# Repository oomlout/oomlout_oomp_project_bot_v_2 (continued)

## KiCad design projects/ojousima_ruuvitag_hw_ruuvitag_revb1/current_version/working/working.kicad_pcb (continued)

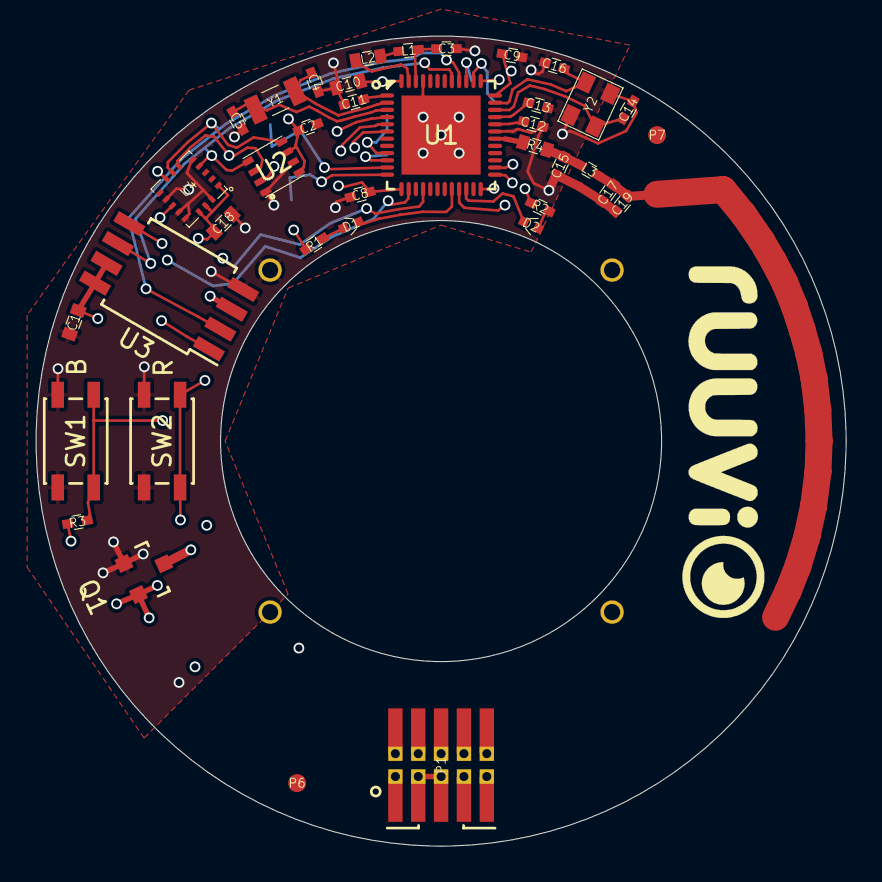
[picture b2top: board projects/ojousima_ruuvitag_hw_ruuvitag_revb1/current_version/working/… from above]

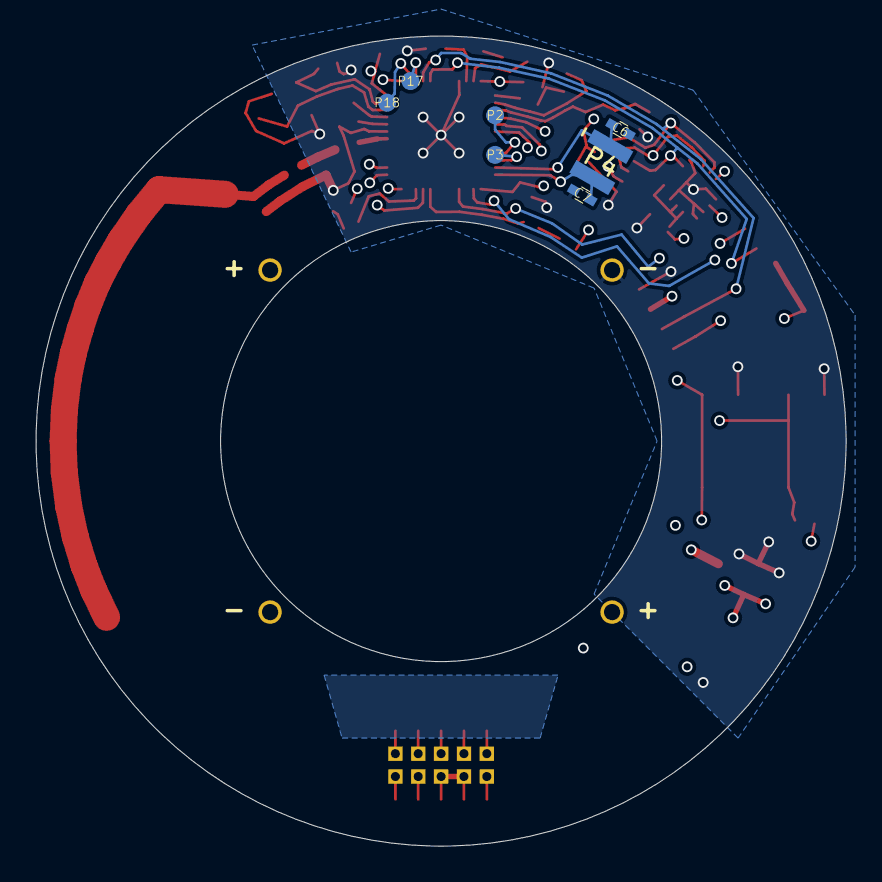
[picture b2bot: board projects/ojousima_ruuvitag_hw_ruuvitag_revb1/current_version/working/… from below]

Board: 4 copper layers, 45.0 x 45.0 mm, 49 parts (7 on the bottom side), 38 nets.

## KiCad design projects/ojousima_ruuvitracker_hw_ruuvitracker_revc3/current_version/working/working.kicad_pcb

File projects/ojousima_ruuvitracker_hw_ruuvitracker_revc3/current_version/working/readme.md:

# ruuvitracker_hw
 
## summary 
* id: ojousima_ruuvitracker_hw_ruuvitracker_revc3
* user: ojousima
* name: ruuvitracker_hw
* board: ruuvitracker_revc3
* repo: https://github.com/ojousima/ruuvitracker_hw
* src_file_repo_kicad_pcb: ruuvitracker_revc3/ruuvitracker_revc3.kicad_pcb
* src_file_repo_kicad_pcb_link: https://github.com/ojousima/ruuvitracker_hw/tree/master/ruuvitracker_revc3/ruuvitracker_revc3.kicad_pcb

* src_file_repo_sch: ruuvitracker_revc3/ruuvitracker_revc3.sch
* src_file_repo_sch_link: https://github.com/ojousima/ruuvitracker_hw/tree/master/ruuvitracker_revc3/ruuvitracker_revc3.sch
* full details link: https://github.com/oomlout/oomlout_oomp_project_bot_v_2/tree/main/projects/ojousima_ruuvitracker_hw_ruuvitracker_revc3/current_version/working

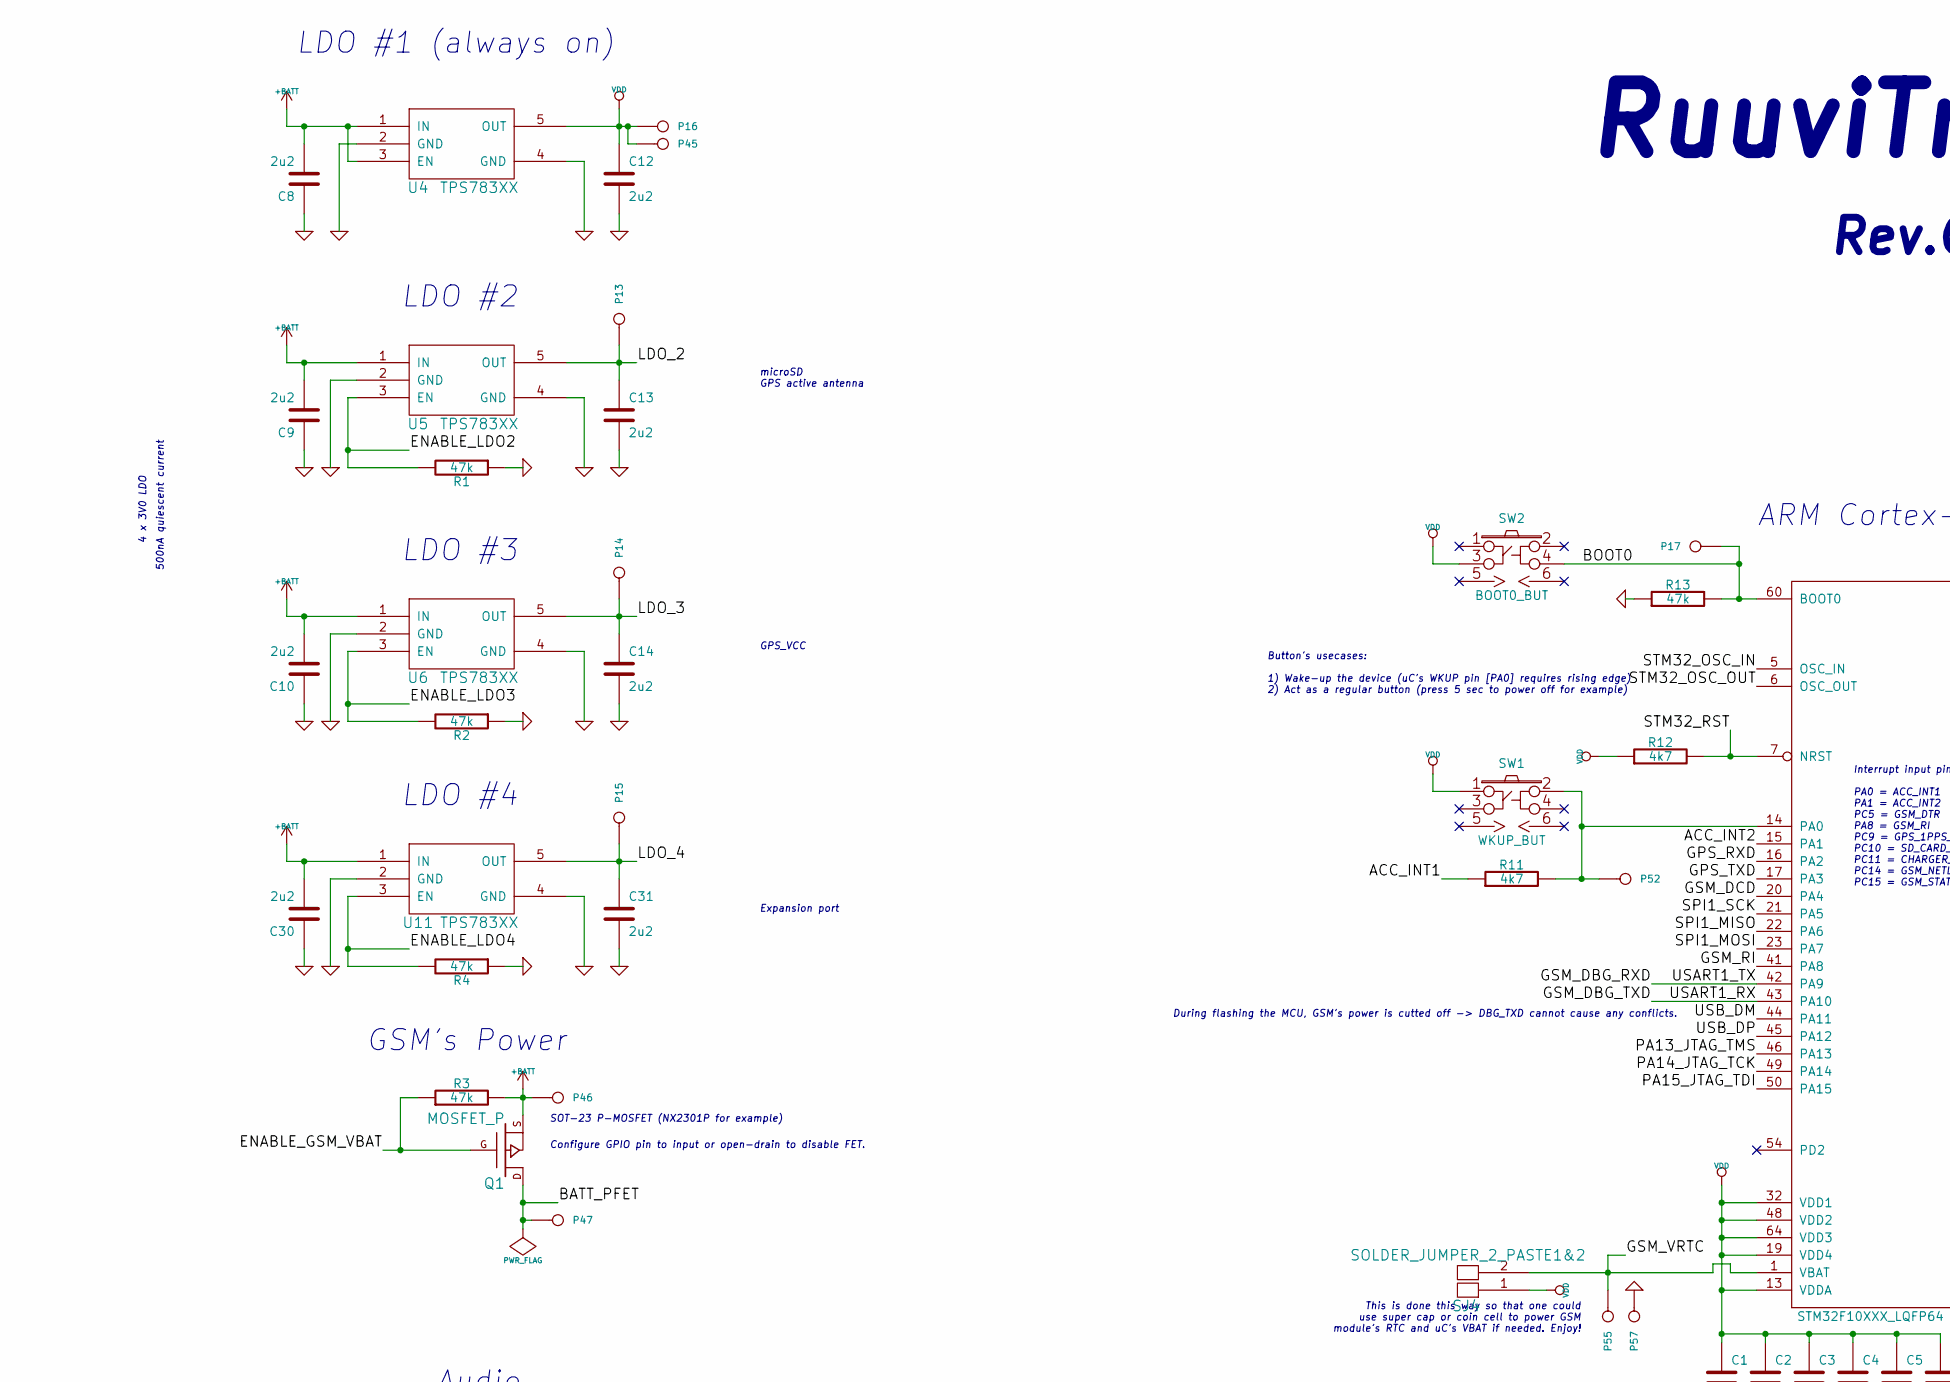
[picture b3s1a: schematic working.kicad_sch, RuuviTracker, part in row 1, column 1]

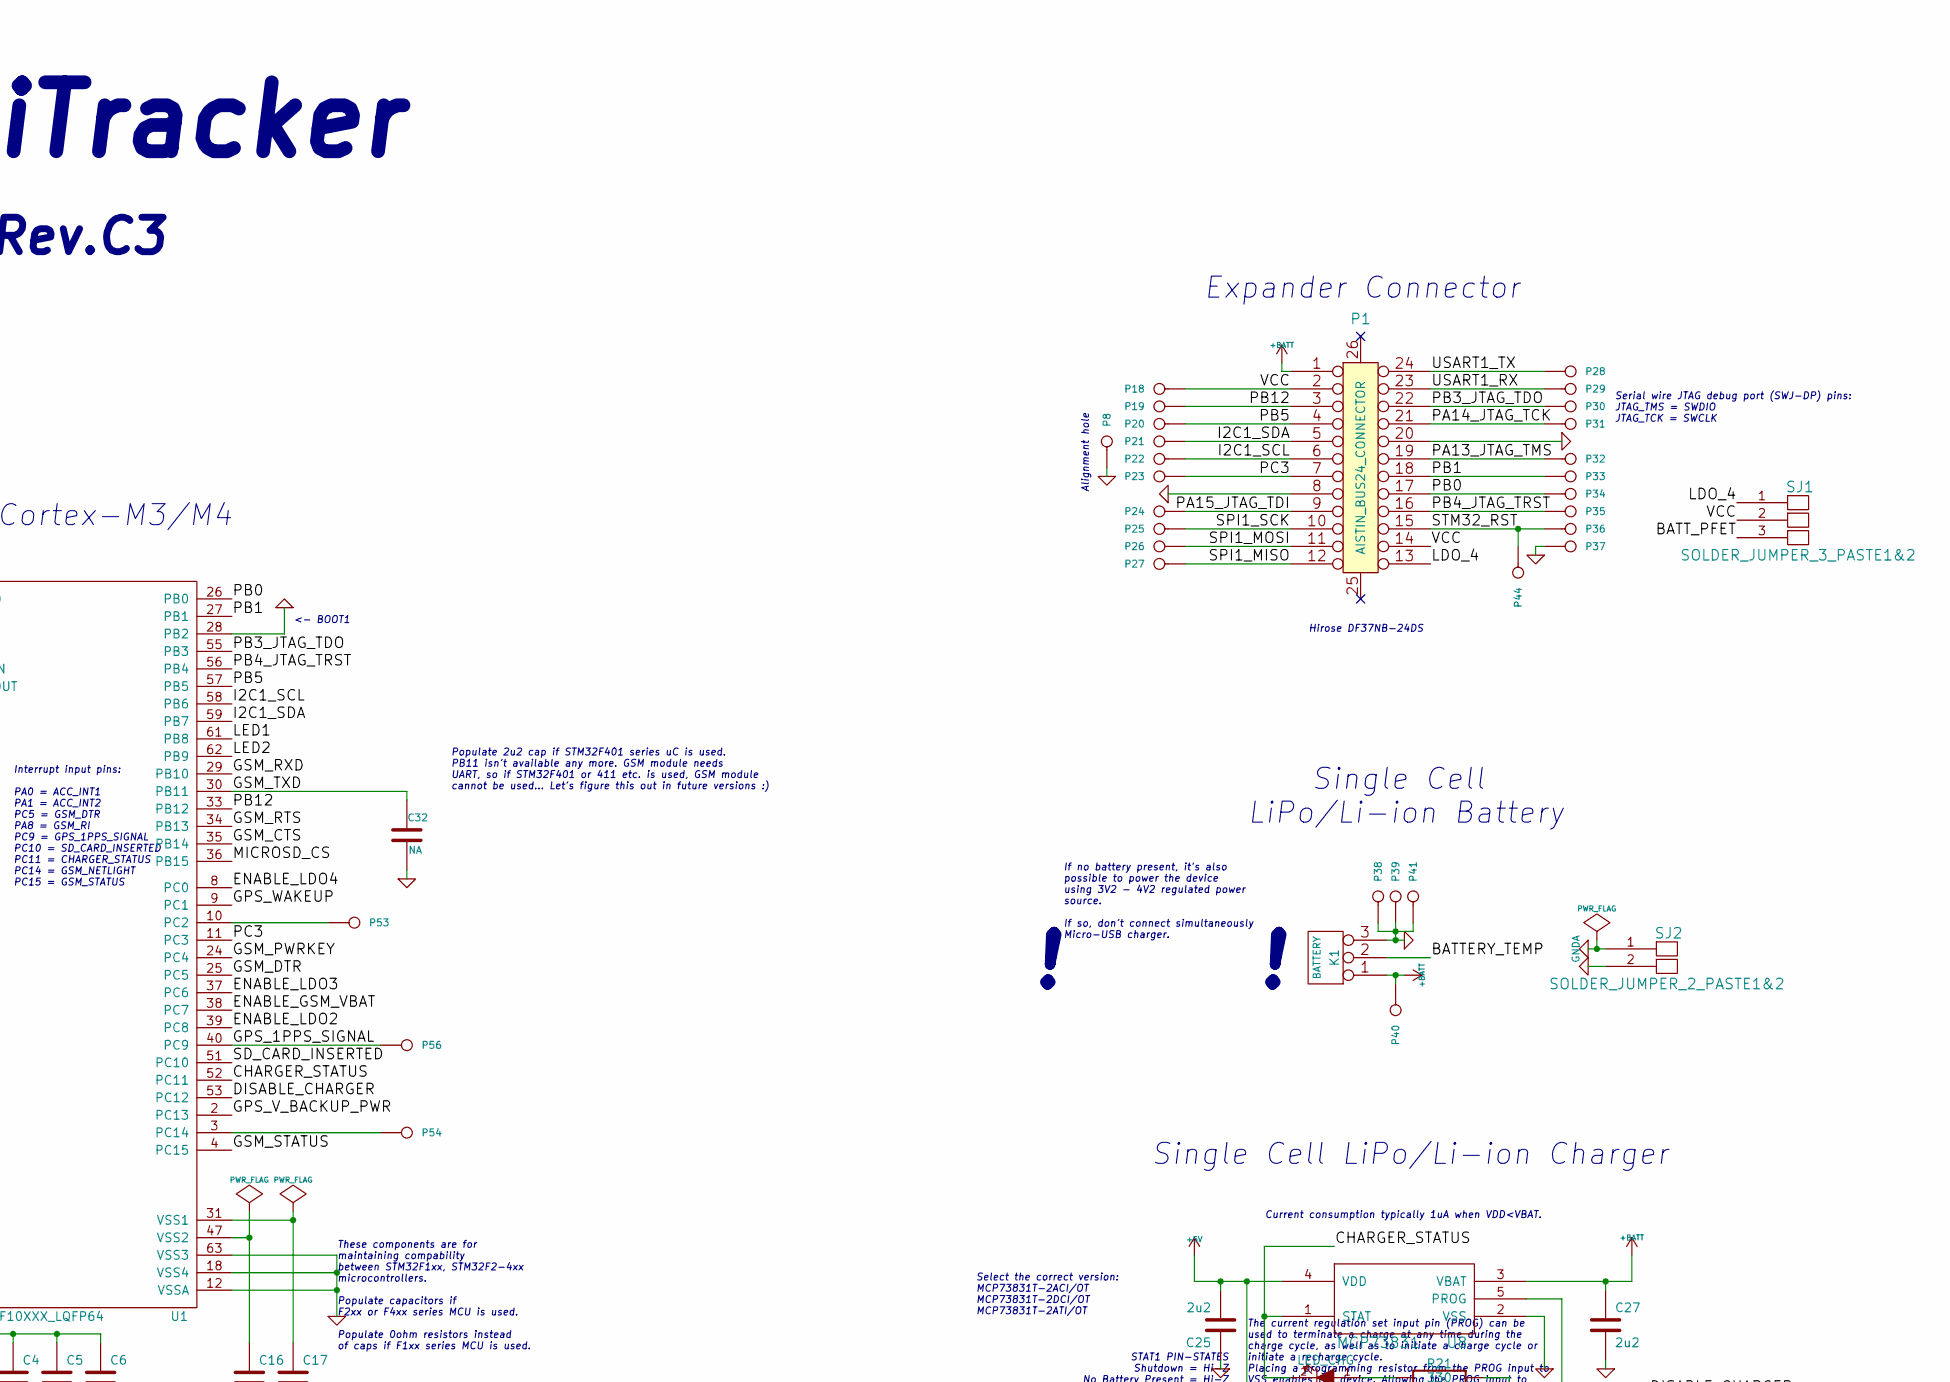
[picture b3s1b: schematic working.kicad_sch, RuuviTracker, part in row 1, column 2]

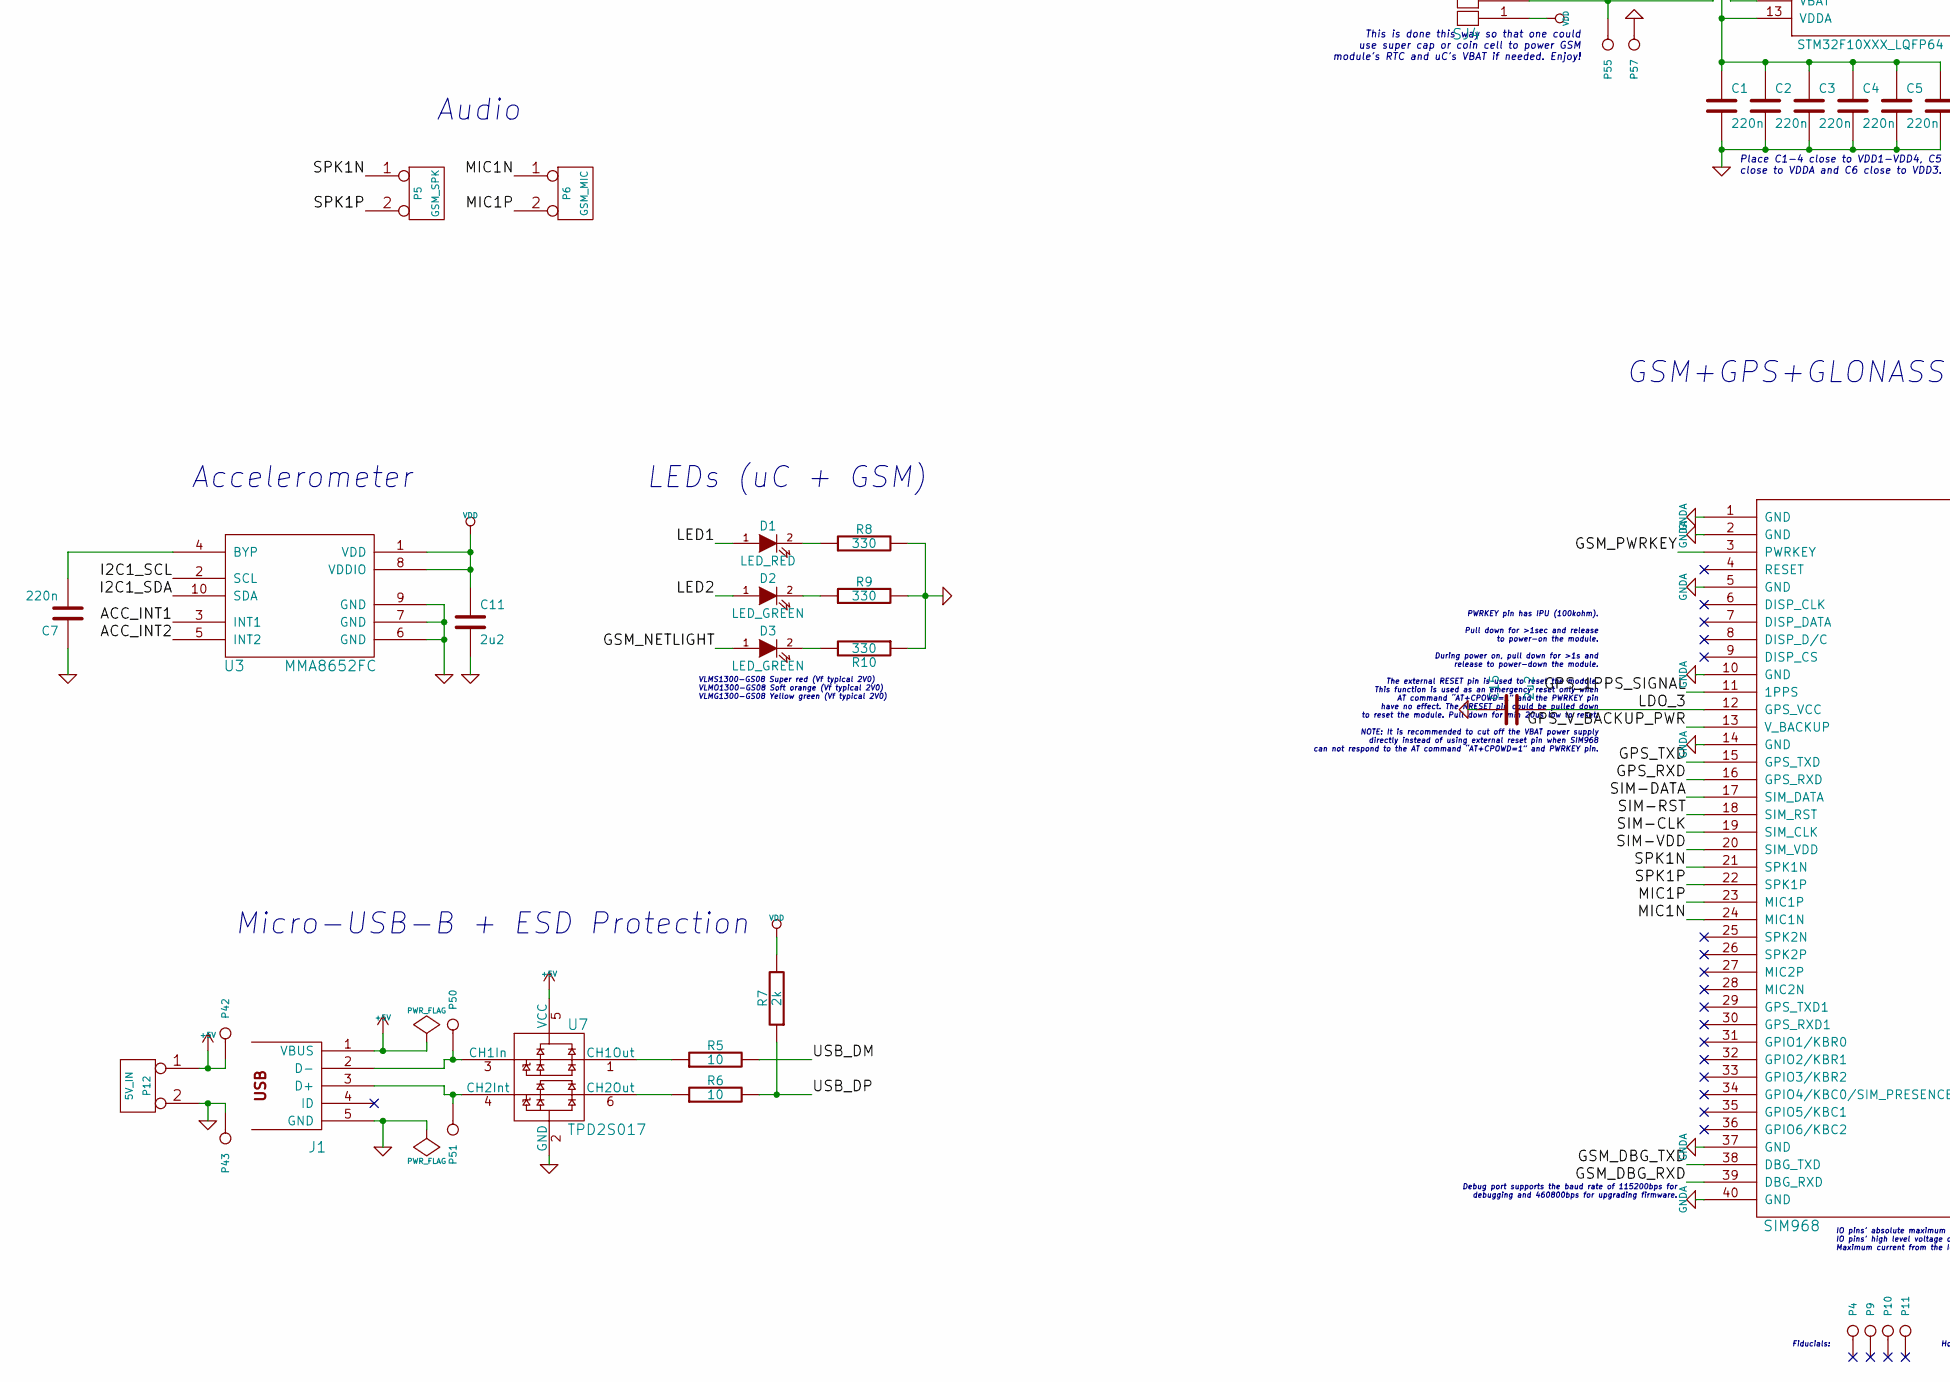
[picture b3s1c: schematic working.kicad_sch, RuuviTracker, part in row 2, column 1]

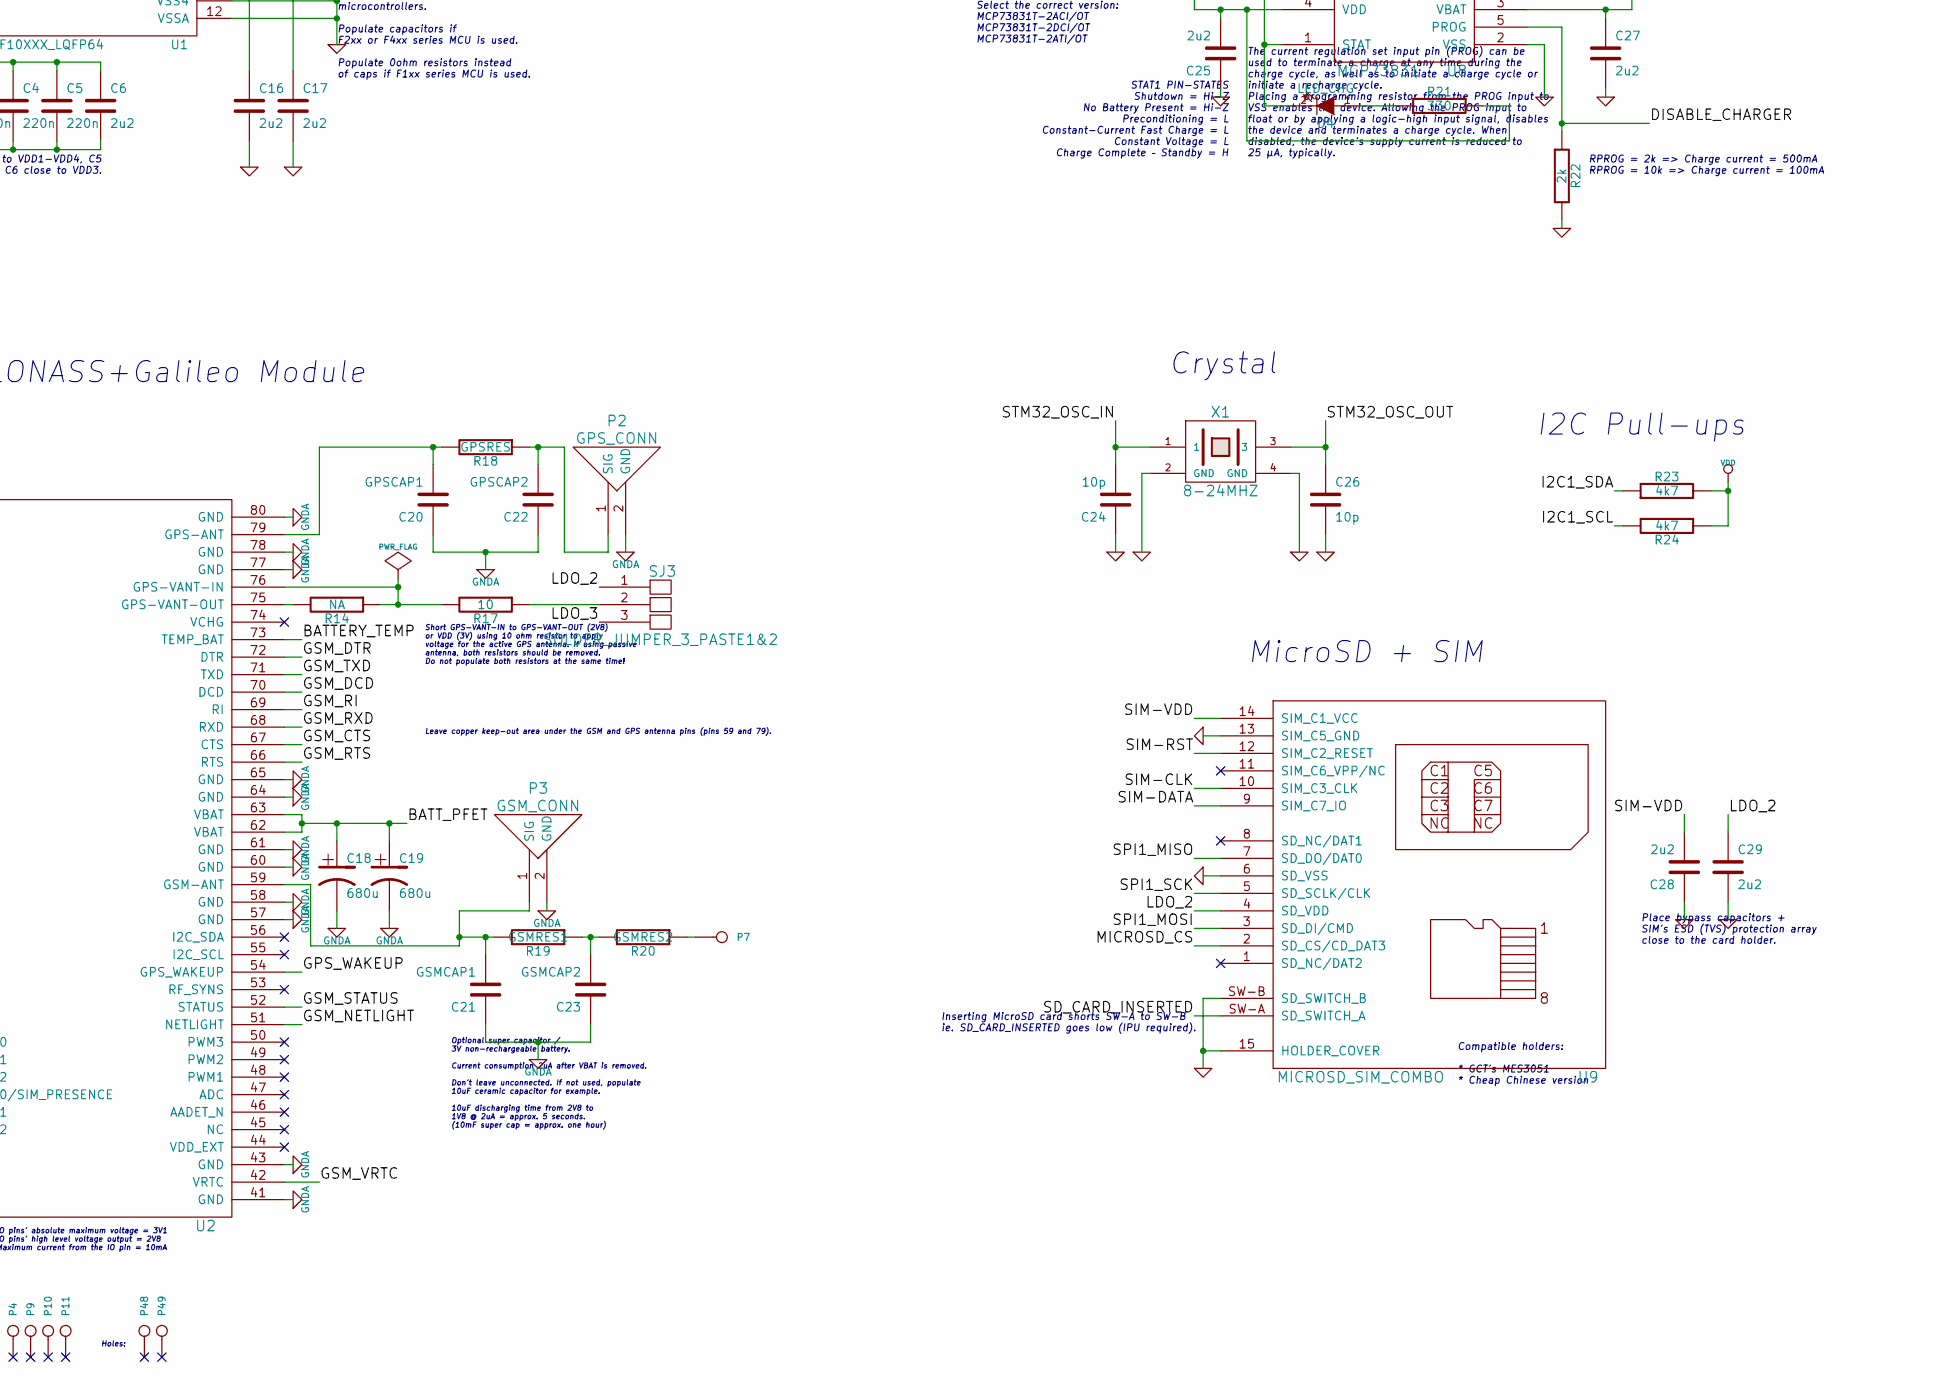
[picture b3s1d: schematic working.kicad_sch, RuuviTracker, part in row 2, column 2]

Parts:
C1, C2, C3, C4, C5, C7: 220n
C6, C8, C9, C10, C11, C12, C13, C14, C15, C16, C17, C25, C27, C28, C29, C30, C31: 2u2
C18, C19: 680u
C20: GPSCAP1
C21: GSMCAP1
C22: GPSCAP2
C23: GSMCAP2
C24, C26: 10p
C32: NA
D1: LED_RED
D2, D3: LED_GREEN
D4: LED_CHG
J1: USB_MICRO_B
K1: BATTERY
P1: AISTIN_BUS24_CONNECTOR
P2: GPS_CONN
P3: GSM_CONN
P4, P9, P10, P11: FIDU
P5: GSM_SPK
P6: GSM_MIC
P7: GSM_ANT
P8: ALIGNMENT
P12: 5V_IN
P13, P14, P15, P16, P17, P18, P19, P20, P21, P22, P23, P24, P25, P26, P27, P28, P29, P30, P31, P32, P33, P34, P35, P36, P37, P38, P39, P40, P41, P42, P43, P44, P45, P46, P47, P50, P51, P52, P53, P54, P55, P56, P57: CONN_1
P48, P49: HOLE
Q1: MOSFET_P
R1, R2, R3, R4, R13: 47k
R5, R6, R17: 10
R7, R22: 2k
R8, R9, R10, R21: 330
R11, R12, R23, R24: 4k7
R14: NA
R18: GPSRES
R19: GSMRES1
R20: GSMRES2
SJ1, SJ3: SOLDER_JUMPER_3_PASTE1&2
SJ2, SJ4: SOLDER_JUMPER_2_PASTE1&2
SW1: WKUP_BUT
SW2: BOOT0_BUT
U1: STM32F10XXX_LQFP64
U2: SIM968
U3: MMA8652FC
U4, U5, U6, U11: TPS783XX
U7: TPD2S017
U8: MCP73831
U9: MICROSD_SIM_COMBO
X1: 8-24MHZ

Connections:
+5V: C25.2, J1.1 (VBUS), P12.1, P42.1, R21.2, U7.5 (VCC), U8.4 (VDD)
+BATT: C8.2, C9.2, C10.2, C27.1, C30.2, K1.1, P1.1, P40.1, P46.1, Q1.S, R3.2, U4.1 (IN), U4.3 (EN), U5.1 (IN), U6.1 (IN), U8.3 (VBAT), U11.1 (IN)
/ACC_INT1: R11.1, U3.3 (INT1)
/ACC_INT2: U1.15 (PA1), U3.5 (INT2)
/BATTERY_TEMP: K1.2 (PM), U2.73 (TEMP_BAT)
/BATT_PFET: C18.1, C19.1, P47.1, Q1.D, SJ1.3, U2.62 (VBAT), U2.63 (VBAT)
/BOOT0: P17.1, R13.2, SW2.4, U1.60 (BOOT0)
/CHARGER_STATUS: D4.2 (K), U1.52 (PC11), U8.1 (STAT)
/DISABLE_CHARGER: R22.1, U1.53 (PC12), U8.5 (PROG)
/ENABLE_GSM_VBAT: Q1.G, R3.1, U1.38 (PC7)
/ENABLE_LDO2: R1.2, U1.39 (PC8), U5.3 (EN)
/ENABLE_LDO3: R2.2, U1.37 (PC6), U6.3 (EN)
/ENABLE_LDO4: R4.2, U1.8 (PC0), U11.3 (EN)
/GPS_1PPS_SIGNAL: P56.1, U1.40 (PC9), U2.11 (1PPS)
/GPS_RXD: U1.16 (PA2), U2.16 (GPS_RXD)
/GPS_TXD: U1.17 (PA3), U2.15 (GPS_TXD)
/GPS_V_BACKUP_PWR: U1.2 (PC13), U2.13 (V_BACKUP)
/GPS_WAKEUP: U1.9 (PC1), U2.54 (GPS_WAKEUP)
/GSM_CTS: U1.35 (PB14), U2.67 (CTS)
/GSM_DBG_RXD: P1.24, P28.1, U1.42 (PA9), U2.39 (DBG_RXD)
/GSM_DBG_TXD: P1.23, P29.1, U1.43 (PA10), U2.38 (DBG_TXD)
/GSM_DCD: U1.20 (PA4), U2.70 (DCD)
/GSM_DTR: U1.25 (PC5), U2.72 (DTR)
/GSM_NETLIGHT: D3.1 (A), U2.51 (NETLIGHT)
/GSM_PWRKEY: U1.24 (PC4), U2.3 (PWRKEY)
/GSM_RI: U1.41 (PA8), U2.69 (RI)
/GSM_RTS: U1.34 (PB13), U2.66 (RTS)
/GSM_RXD: U1.29 (PB10), U2.68 (RXD)
/GSM_STATUS: U1.4 (PC15), U2.52 (STATUS)
/GSM_TXD: C32.1, U1.30 (PB11), U2.71 (TXD)
/GSM_VRTC: P55.1, SJ4.2, U1.1 (VBAT), U2.42 (VRTC)
/I2C1_SCL: P1.6, P22.1, R24.2, U1.58 (PB6), U3.2 (SCL)
/I2C1_SDA: P1.5, P21.1, R23.1, U1.59 (PB7), U3.10 (SDA)
/LDO_2: C13.1, C29.1, P13.1, SJ3.1, U5.5 (OUT), U9.4 (SD_VDD)
/LDO_3: C14.1, C15.2, P14.1, SJ3.3, U2.12 (GPS_VCC), U6.5 (OUT)
/LDO_4: C31.1, P1.13, P15.1, SJ1.1, U11.5 (OUT)
/LED1: D1.1 (A), U1.61 (PB8)
/LED2: D2.1 (A), U1.62 (PB9)
/MIC1N: P6.1, U2.24 (MIC1N)
/MIC1P: P6.2 (PM), U2.23 (MIC1P)
/MICROSD_CS: U1.36 (PB15), U9.2 (SD_CS/CD_DAT3)
/PA13_JTAG_TMS: P1.19, P32.1, U1.46 (PA13)
/PA14_JTAG_TCK: P1.21, P31.1, U1.49 (PA14)
/PA15_JTAG_TDI: P1.9, P24.1, U1.50 (PA15)
/PB0: P1.17, P34.1, U1.26 (PB0)
/PB1: P1.18, P33.1, U1.27 (PB1)
/PB3_JTAG_TDO: P1.22, P30.1, U1.55 (PB3)
/PB4_JTAG_TRST: P1.16, P35.1, U1.56 (PB4)
/PB5: P1.4, P20.1, U1.57 (PB5)
/PB12: P1.3, P19.1, U1.33 (PB12)
/PC3: P1.7, P23.1, U1.11 (PC3)
/SD_CARD_INSERTED: U1.51 (PC10), U9.SW-A (SD_SWITCH_A)
/SIM-CLK: U2.19 (SIM_CLK), U9.10 (SIM_C3_CLK)
/SIM-DATA: U2.17 (SIM_DATA), U9.9 (SIM_C7_IO)
/SIM-RST: U2.18 (SIM_RST), U9.12 (SIM_C2_RESET)
/SIM-VDD: C28.2, U2.20 (SIM_VDD), U9.14 (SIM_C1_VCC)
/SPI1_MISO: P1.12, P27.1, U1.22 (PA6), U9.7 (SD_DO/DAT0)
/SPI1_MOSI: P1.11, P26.1, U1.23 (PA7), U9.3 (SD_DI/CMD)
/SPI1_SCK: P1.10, P25.1, U1.21 (PA5), U9.5 (SD_SCLK/CLK)
/SPK1N: P5.1, U2.21 (SPK1N)
/SPK1P: P5.2 (PM), U2.22 (SPK1P)
/STM32_OSC_IN: C24.2, U1.5 (OSC_IN), X1.1
/STM32_OSC_OUT: C26.1, U1.6 (OSC_OUT), X1.3
/STM32_RST: P1.15, P36.1, P44.1, R12.2, U1.7 (NRST)
/USB_DM: R5.2, U1.44 (PA11)
/USB_DP: R6.2, R7.1, U1.45 (PA12)
/VCC: P1.2, P1.14, P18.1, SJ1.2
GND: C1.2, C2.2, C3.2, C4.2, C5.2, C6.2, C7.1, C8.1, C9.1, C10.1, C11.2, C12.2, C13.2, C14.2, C15.1, C16.2, C17.2, C24.1, C25.1, C26.2, C27.2, C28.1, C29.2, C30.1, C31.2, C32.2, J1.5 (GND), K1.3, P1.8, P1.20, P8.1, P12.2 (PM), P37.1, P38.1, P39.1, P41.1, P43.1, P57.1, R1.1, R2.1, R4.1, R8.2, R9.2, R10.1, R13.1, R22.2, SJ2.2, U1.12 (VSSA), U1.18 (VSS4), U1.28 (PB2), U1.63 (VSS3), U3.6 (GND), U3.7 (GND), U3.9 (GND), U4.2 (GND), U4.4 (GND), U5.2 (GND), U5.4 (GND), U6.2 (GND), U6.4 (GND), U7.2 (GND), U8.2 (VSS), U9.6 (SD_VSS), U9.13 (SIM_C5_GND), U9.15 (HOLDER_COVER), U9.SW-B (SD_SWITCH_B), U11.2 (GND), U11.4 (GND), X1.2 (GND), X1.4 (GND)
GNDA: C18.2, C19.2, C20.1, C21.1, C22.1, C23.1, P2.2 (GND), P3.2 (GND), SJ2.1, U2.1 (GND), U2.2 (GND), U2.5 (GND), U2.10 (GND), U2.14 (GND), U2.37 (GND), U2.40 (GND), U2.41 (GND), U2.43 (GND), U2.57 (GND), U2.58 (GND), U2.60 (GND), U2.61 (GND), U2.64 (GND), U2.65 (GND), U2.77 (GND), U2.78 (GND), U2.80 (GND)
unnamed: P52.1, R11.2, SW1.2, U1.14 (PA0)
unnamed: C16.1, U1.47 (VSS2)
unnamed: C17.1, U1.31 (VSS1)
unnamed: C20.2, R18.2, U2.79 (GPS-ANT)
unnamed: C22.2, P2.1 (SIG), R18.1
unnamed: R17.1, SJ3.2
unnamed: R14.2, U2.75 (GPS-VANT-OUT)
unnamed: R14.1, R17.2, U2.76 (GPS-VANT-IN)
unnamed: P53.1, U1.10 (PC2)
unnamed: P54.1, U1.3 (PC14)
unnamed: J1.3 (D+), P51.1, U7.4 (CH2Int)
unnamed: C21.2, P3.1 (SIG), R19.2, U2.59 (GSM-ANT)
unnamed: C23.2, R19.1, R20.2
unnamed: P7.1, R20.1
unnamed: R6.1, U7.6 (CH2Out)
unnamed: R5.1, U7.1 (CH1Out)
unnamed: J1.2 (D-), P50.1, U7.3 (CH1In)
unnamed: D3.2 (K), R10.2
unnamed: D1.2 (K), R8.1
unnamed: D2.2 (K), R9.1
unnamed: C7.2, U3.4 (BYP)
unnamed: D4.1 (A), R21.1
VDD: C1.1, C2.1, C3.1, C4.1, C5.1, C6.1, C11.1, C12.1, P16.1, P45.1, R7.2, R12.1, R23.2, R24.1, SJ4.1, SW1.1, SW2.3, U1.13 (VDDA), U1.19 (VDD4), U1.32 (VDD1), U1.48 (VDD2), U1.64 (VDD3), U3.1 (VDD), U3.8 (VDDIO), U4.5 (OUT)

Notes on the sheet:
<- BOOT1
4 x 3V0 LDO
GSM's Power
Compatible holders: * GCT's MES3051 * Cheap Chinese version
LEDs (uC + GSM)
Place C1-4 close to VDD1-VDD4, C5 close to VDDA and C6 close to VDD3.
Expander Connector
! !
Holes:
MicroSD + SIM
Leave copper keep-out area under the GSM and GPS antenna pins (pins 59 and 79).
500nA quiescent current
Short GPS-VANT-IN to GPS-VANT-OUT (2V8) or VDD (3V) using 10 ohm resistor to apply voltage for the active GPS antenna. If using passive antenna, both resistors should be removed. Do not populate both resistors at the same time!
SOT-23 P-MOSFET (NX2301P for example)
Single Cell LiPo/Li-ion Battery
Populate 2u2 cap if STM32F401 series uC is used. PB11 isn't available any more. GSM module needs UART, so if STM32F401 or 411 etc. is used, GSM module cannot be used... Let's figure this out in future versions :)
GPS_VCC
Crystal
These components are for maintaining compability between STM32F1xx, STM32F2-4xx microcontrollers. Populate capacitors if F2xx or F4xx series MCU is used. Populate 0ohm resistors instead of caps if F1xx series MCU is used.
If no battery present, it's also possible to power the device using 3V2 - 4V2 regulated power source. If so, don't connect simultaneously Micro-USB charger.
Alignment hole
Accelerometer
Rev.C3
GSM+GPS+GLONASS+Galileo Module
Fiducials:
LDO #1 (always on)
RuuviTracker
RPROG = 2k => Charge current = 500mA RPROG = 10k => Charge current = 100mA
Micro-USB-B + ESD Protection
LDO #2
VLMS1300-GS08 Super red (Vf typical 2V0) VLMO1300-GS08 Soft orange (Vf typical 2V0) VLMG1300-GS08 Yellow green (Vf typical 2V0)
microSD GPS active antenna
Serial wire JTAG debug port (SWJ-DP) pins: JTAG_TMS = SWDIO JTAG_TCK = SWCLK
Audio
LDO #4
Single Cell LiPo/Li-ion Charger
Optional super capacitor / 3V non-rechargeable battery. Current consumption 2uA after VBAT is removed. Don't leave unconnected. If not used, populate 10uF ceramic capacitor for example. 10uF discharging time from 2V8 to 1V8 @ 2uA = approx. 5 seconds. (10mF super cap = approx. one hour)
During flashing the MCU, GSM's power is cutted off -> DBG_TXD cannot cause any conflicts.
Place bypass capacitors + SIM's ESD (TVS) protection array close to the card holder.
Select the correct version: MCP73831T-2ACI/OT MCP73831T-2DCI/OT MCP73831T-2ATI/OT

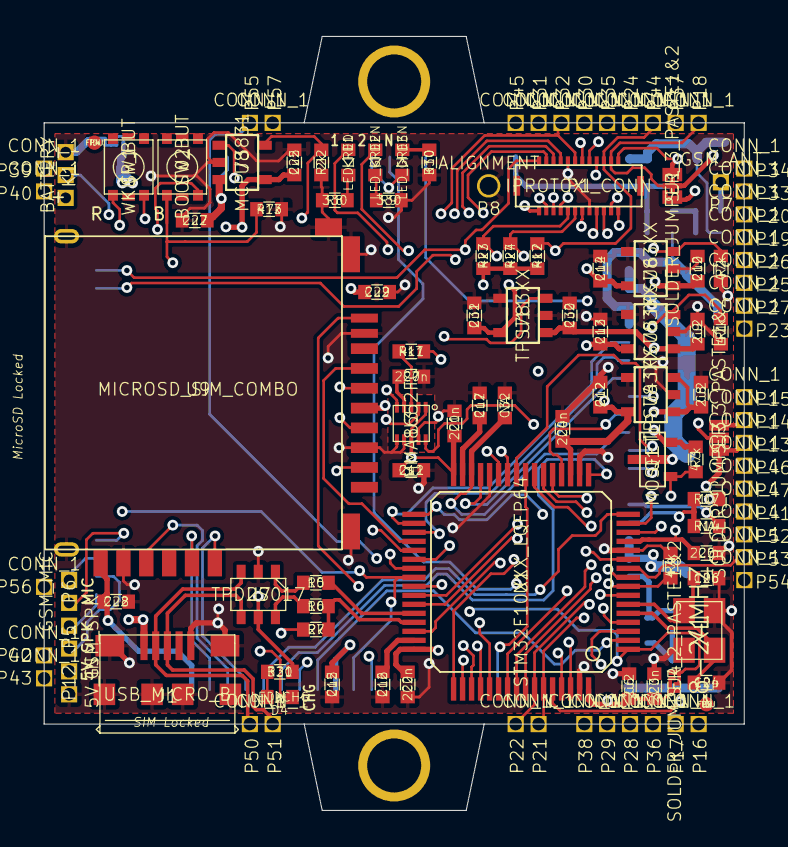
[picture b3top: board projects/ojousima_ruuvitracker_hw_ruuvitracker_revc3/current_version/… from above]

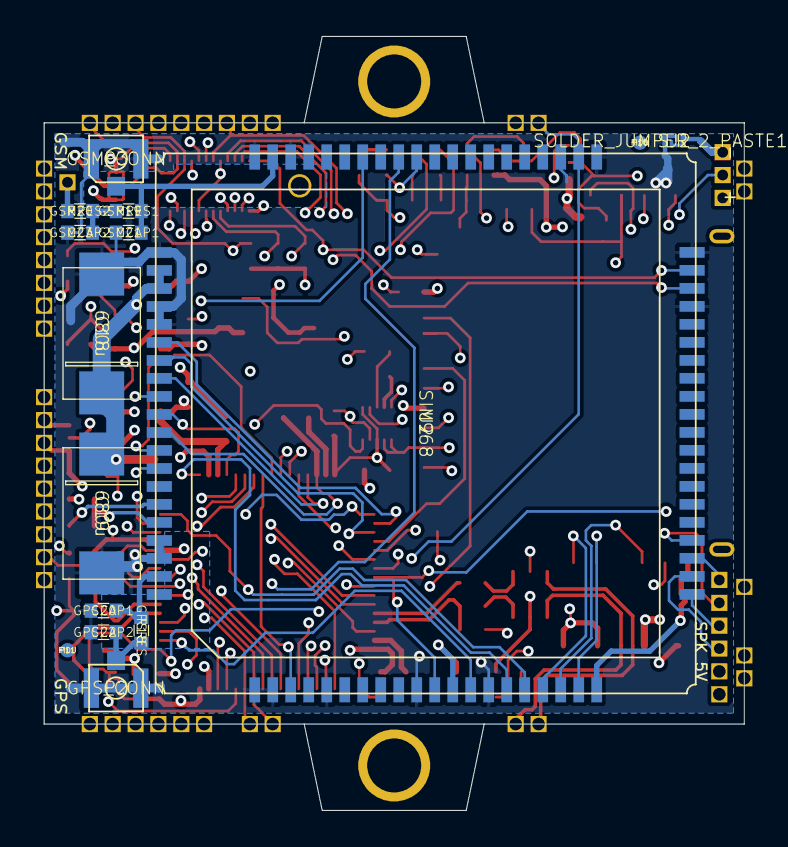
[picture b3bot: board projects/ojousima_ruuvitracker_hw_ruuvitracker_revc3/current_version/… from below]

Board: 6 copper layers, 38.9 x 33.4 mm, 135 parts (15 on the bottom side), 92 nets.

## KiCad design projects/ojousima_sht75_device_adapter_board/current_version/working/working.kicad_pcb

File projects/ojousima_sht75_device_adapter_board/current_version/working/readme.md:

# sht75_device
 
## summary 
* id: ojousima_sht75_device_adapter_board
* user: ojousima
* name: sht75_device
* board: adapter_board
* repo: https://github.com/ojousima/SHT75-device
* src_file_repo_kicad_pcb: PCB/adapter_board.kicad_pcb
* src_file_repo_kicad_pcb_link: https://github.com/ojousima/SHT75-device/tree/master/PCB/adapter_board.kicad_pcb

* src_file_repo_sch: PCB/adapter_board.sch
* src_file_repo_sch_link: https://github.com/ojousima/SHT75-device/tree/master/PCB/adapter_board.sch
* full details link: https://github.com/oomlout/oomlout_oomp_project_bot_v_2/tree/main/projects/ojousima_sht75_device_adapter_board/current_version/working

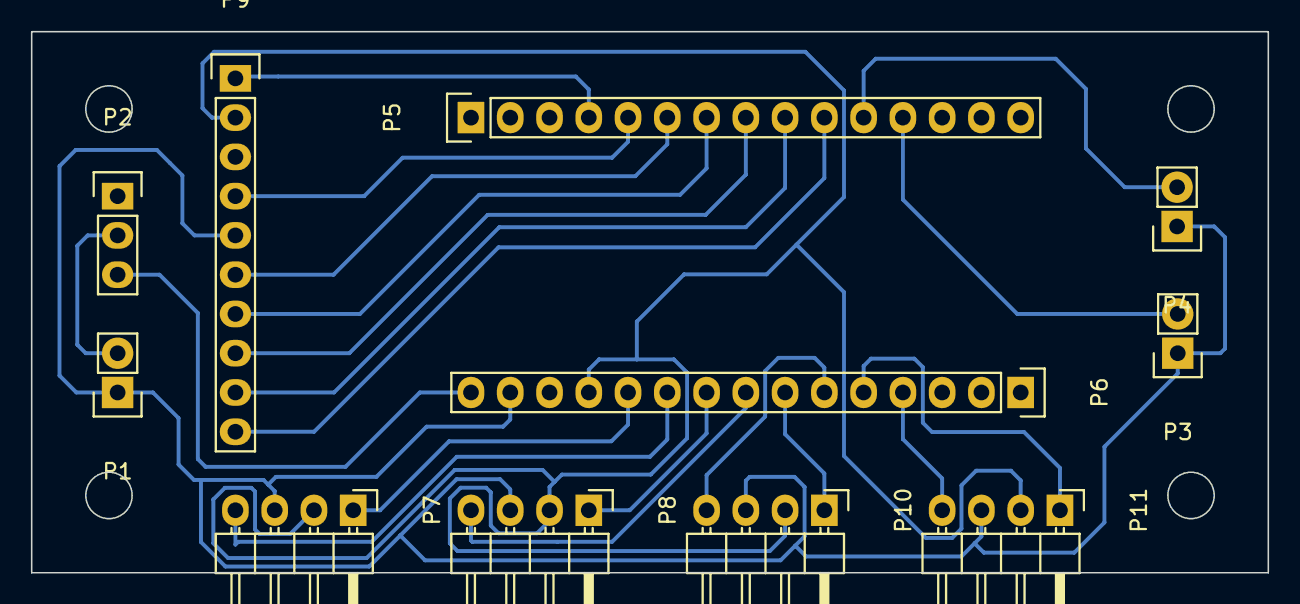
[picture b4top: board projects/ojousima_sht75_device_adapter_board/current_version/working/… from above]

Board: 4 copper layers, 80.0 x 35.0 mm, 11 parts (0 on the bottom side), 21 nets.

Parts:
P1, P3, P4: CONN_01X02; Pin_Header_Straight_1x02
P2: CONN_01X03; Pin_Header_Straight_1x03
P5, P6: CONN_01X15; Pin_Header_Straight_1x15
P7, P8, P10, P11: CONN_01X04; Pin_Header_Angled_1x04
P9: CONN_01X10; Pin_Header_Straight_1x10

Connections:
/BATT_9V: P1.2, P2.2
/BT0: P4.2, P5.11
/BT1: P3.2, P5.12
/D4: P5.7, P9.7
/D5: P5.8, P9.8
/D6: P5.9, P9.9
/D7: P5.10, P9.10
/ENABLE: P5.6, P9.6
/RESET: P5.3, P6.13
/RS: P5.5, P9.4
/SCL0: P6.5, P11.1
/SCL1: P6.7, P10.1
/SCL2: P6.9, P8.1
/SCL3: P6.11, P7.1
/SDA0: P6.4, P11.4
/SDA1: P6.6, P10.4
/SDA2: P6.8, P8.4
/SDA3: P6.10, P7.4
/VCC: P6.12, P7.2, P8.2, P9.2, P10.2, P11.2
/VIN: P2.3, P6.15
GND: P1.1, P3.1, P4.1, P5.4, P6.14, P7.3, P8.3, P9.1, P9.5, P10.3, P11.3

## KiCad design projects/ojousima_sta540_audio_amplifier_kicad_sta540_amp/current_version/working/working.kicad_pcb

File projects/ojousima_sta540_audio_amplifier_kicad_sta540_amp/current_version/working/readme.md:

# sta540_audio_amplifier_kicad
 
## summary 
* id: ojousima_sta540_audio_amplifier_kicad_sta540_amp
* user: ojousima
* name: sta540_audio_amplifier_kicad
* board: sta540_amp
* repo: https://github.com/ojousima/STA540-audio-amplifier---KICAD
* src_file_repo_kicad_pcb: sta540_amp.kicad_pcb
* src_file_repo_kicad_pcb_link: https://github.com/ojousima/STA540-audio-amplifier---KICAD/tree/master/sta540_amp.kicad_pcb

* src_file_repo_sch: sta540_amp.sch
* src_file_repo_sch_link: https://github.com/ojousima/STA540-audio-amplifier---KICAD/tree/master/sta540_amp.sch
* full details link: https://github.com/oomlout/oomlout_oomp_project_bot_v_2/tree/main/projects/ojousima_sta540_audio_amplifier_kicad_sta540_amp/current_version/working

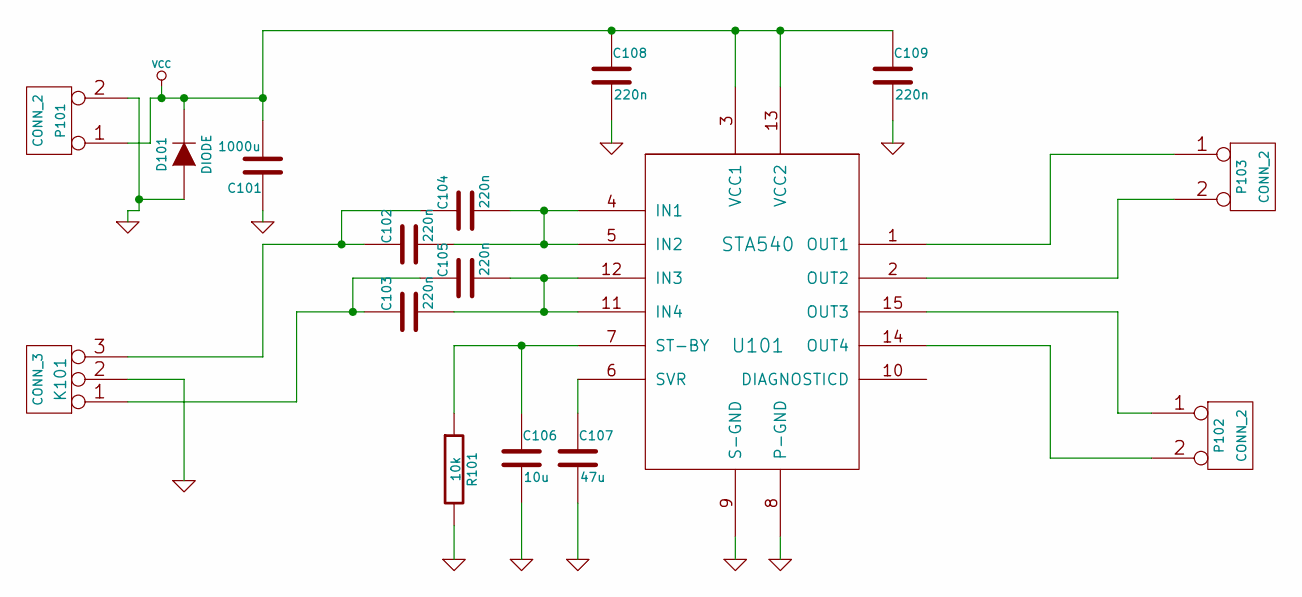
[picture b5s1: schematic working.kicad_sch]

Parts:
C101: 1000u
C102, C103, C104, C105, C108, C109: 220n
C106: 10u
C107: 47u
D101: DIODE
K101: CONN_3
P101, P102, P103: CONN_2
R101: 10k
U101: STA540

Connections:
GND: C101.1, C106.2, C107.2, C108.2, C109.2, D101.1 (A), K101.2 (PM), P101.2 (PM), R101.2, U101.8 (P-GND), U101.9 (S-GND)
unnamed: C106.1, R101.1, U101.7 (ST-BY)
unnamed: C107.1, U101.6 (SVR)
unnamed: C103.2, C105.2, U101.11 (IN4), U101.12 (IN3)
unnamed: P102.1, U101.15 (OUT3)
unnamed: P103.1, U101.1 (OUT1)
unnamed: P103.2 (PM), U101.2 (OUT2)
unnamed: P102.2 (PM), U101.14 (OUT4)
unnamed: C102.2, C104.2, U101.4 (IN1), U101.5 (IN2)
unnamed: C103.1, C105.1, K101.1
unnamed: C102.1, C104.1, K101.3
VCC: C101.2, C108.1, C109.1, D101.2 (K), P101.1, U101.3 (VCC1), U101.13 (VCC2)
